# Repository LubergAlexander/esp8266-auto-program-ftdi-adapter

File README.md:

# Description

Test esp8266 autoprogramming board for FTDI breakout board.

# 3D Render

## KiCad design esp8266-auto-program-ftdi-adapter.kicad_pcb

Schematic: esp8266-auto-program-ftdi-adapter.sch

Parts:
J1, J2: Conn_01x09_Female; PinHeader_1x09_P2.54mm_Vertical
J3: Conn_01x06_Male; PinHeader_1x06_P2.54mm_Horizontal
Q1, Q2: S8050; TO-92_Inline_W4.0mm_Horizontal_FlatSideDown
R1, R2: 12k; R_Axial_DIN0207_L6.3mm_D2.5mm_P7.62mm_Horizontal
R3: 4.7k; R_Axial_DIN0207_L6.3mm_D2.5mm_P7.62mm_Horizontal

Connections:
+3V3: J2.5, J3.5, R3.1
/DTR: J1.8, Q2.1 (E), R1.2
/GPIO0: J3.3, Q2.3 (C), R3.2
/RESET: J3.4, Q1.3 (C)
/RTS: J1.7, Q1.1 (E), R2.2
/RXD: J1.5, J3.1
/TXD: J1.9, J3.2
GND: J2.1, J3.6
unnamed: Q1.2 (B), R1.1
unnamed: Q2.2 (B), R2.1

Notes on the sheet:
NodeMCUs autoreset
Headers for FTDI - USB adapter
ESP8266 header for autoprogramming
TODO: Correct pin order

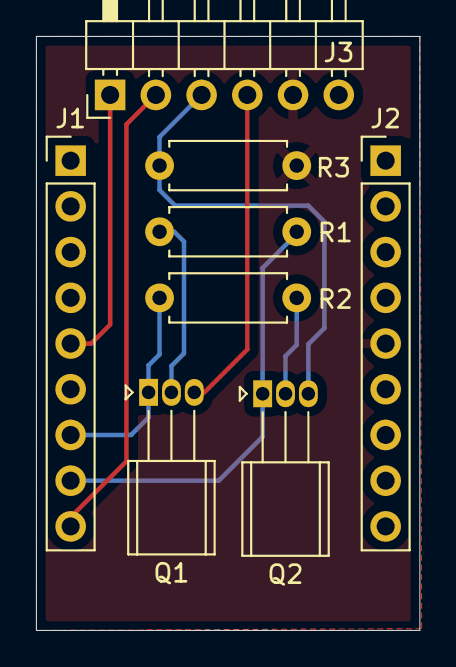
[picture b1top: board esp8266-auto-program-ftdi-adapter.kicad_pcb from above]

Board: 2 copper layers, 21.3 x 33.0 mm, 8 parts (0 on the bottom side), 10 nets.

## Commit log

2020-01-02 Project init
2020-01-03 Adapter for FTDI breakout board
2020-01-03 Added readme
2020-01-03 Fixed ci workflow
2020-01-03 Added pic
